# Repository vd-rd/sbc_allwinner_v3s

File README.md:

# Allwinner V3s SBC

This board embeds a SIP (single core 1GHz Cortex-A7 with 64MB DDR2) with AXP203 PMIC, IO headers and microSD/eMMC storage.

Board overview (draft):
[TBD]

## Board features
| Characteristic | Description |
| --- | --- |
| Dimensions | 60mm x 40mm |
| Processor | Allwinner V3s Cortex-A7 @1GHz |
| Oscillators | 32.768kHz slow click, 24MHz main clock |
| RAM | 512Mb embedded DDR2 memory |
| Storage | SPI Flash/microSD |
| USB | 1 microUSB OTG |
| Ethernet | 10/100M PHY with pins on header |
| Supply | Power path between USB/Vin/Battery, 5V max |

## Notes and observations

### Expansions
The board features a number of connectors. They expose various buses for expansions:
 * 1 SPI port
 * 2 UART ports
 * 1 I2C port
 * 2 ADC enabled pins
 * 18bit parallel LCD interface
 * Ethernet signals with status LEDs

The connectors are organized in consistent locations present on the other SBCs i have developed.
 * J100 connector - 2.54mm 2x18 header with standard Apollo IoT pinout
 * J200 connector - 1.27mm 2x04 header with ethernet signals
 * J300 connector - 1.27mm 2x05 header with analog audio I/O signals
 * J500 connector - 1.27mm 2x20 header with parallel LCD interface signals

Check expansions section for example daughter cards with added functionality

### Boot process
The board has two boot strategies depending on component configuration. If the SPI flash memory is not used, the BROM uses the MicroSD as boot source and loads UBoot from there.
If the SPI flash is populated, UBoot with a minimal Kernel and Busybox can be stored as recovery environment or main application.

### LCD connector
Most of port D signals are mapped to the LCD connector. if LCD is not used they can be muxed as GPIO or other functions upon editing the DT overlay.

### AXP203
AXP203 is pin to pin compatible with the more popular AXP209, so they can be easily swapped.

### 1.2V Rail
Two different 1.2V rails are provided to the CPU. This is a deliberate decision to allow fixed CPU internal rail at 1.2V and provide DVFS cappability to 1.2V rail for CPU core.

### Signals on headers
All the signals on the headers, with their initial functions are detailed on the silkscreen on the bottom layer

### Battery usage
The board schematic uses a Diodes AP9211 battery protection IC for safety protections when used toghether with a LiIon battery. If a battery pack with embedded protection and thermistor is used, TH1 and AP9211 can be left unpopulated.

### Expansions
 The board can be combined with several predefined capes that add functionality.
 * [LCD cape](https://github.com/vd-rd/hw_cape_lcd) can be used to add a 3inch LCD/Touch with 800x480px resolution.
 * [GPS cape](https://github.com/vd-rd/hw_cape_gps) adds GPS/GNSS/GLONAS capabilities
 * [GSM cape](https://github.com/vd-rd/hw_cape_gsm) adds GPRS connectivity. 

## Resources
You can find all necesary information to build or evaluate the module here:
   - [View 3D board render](https://a360.co/2GTPupk)
   - [Fabrication files](https://github.com/vd-rd/sbc_alw_v3s/releases)

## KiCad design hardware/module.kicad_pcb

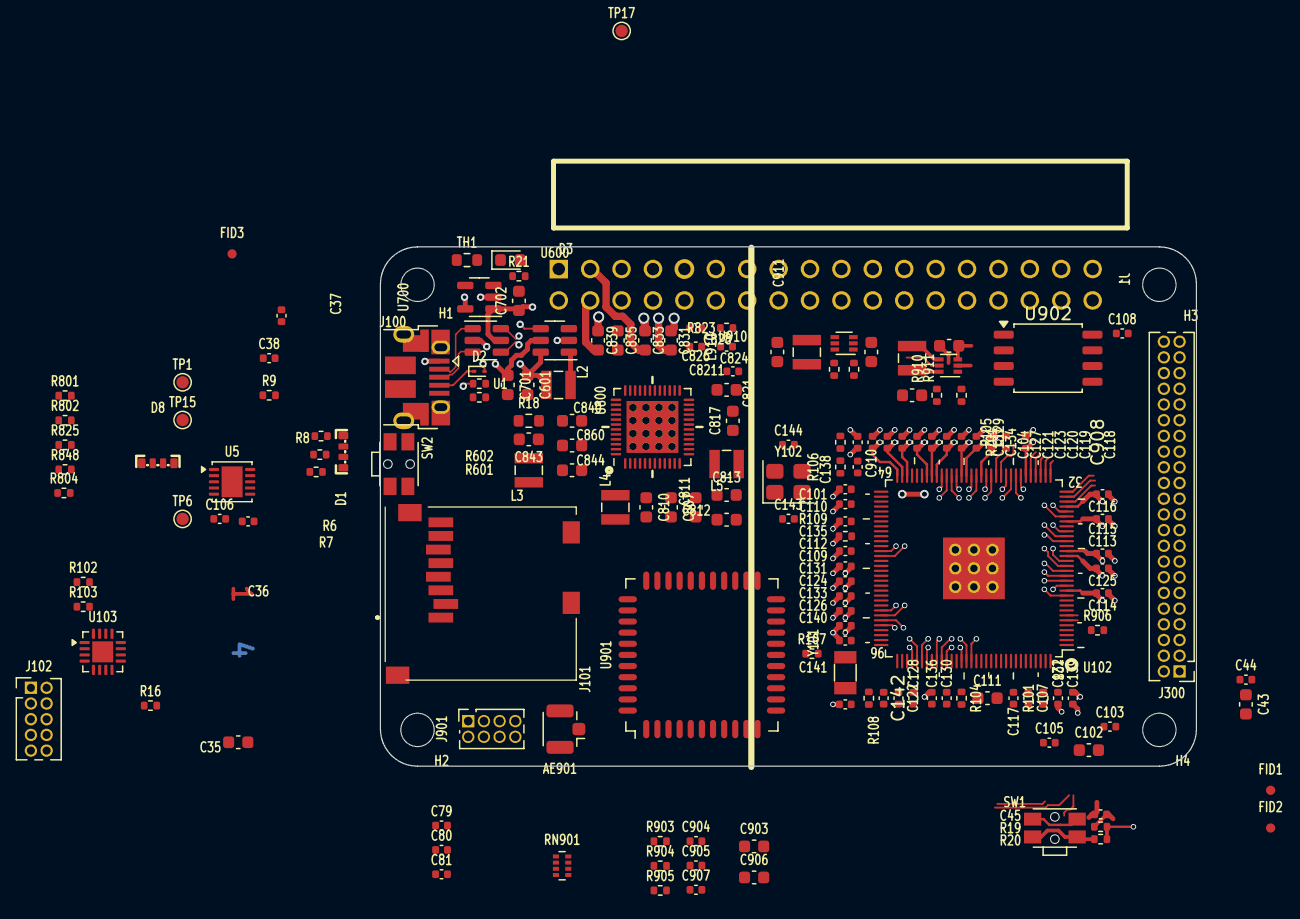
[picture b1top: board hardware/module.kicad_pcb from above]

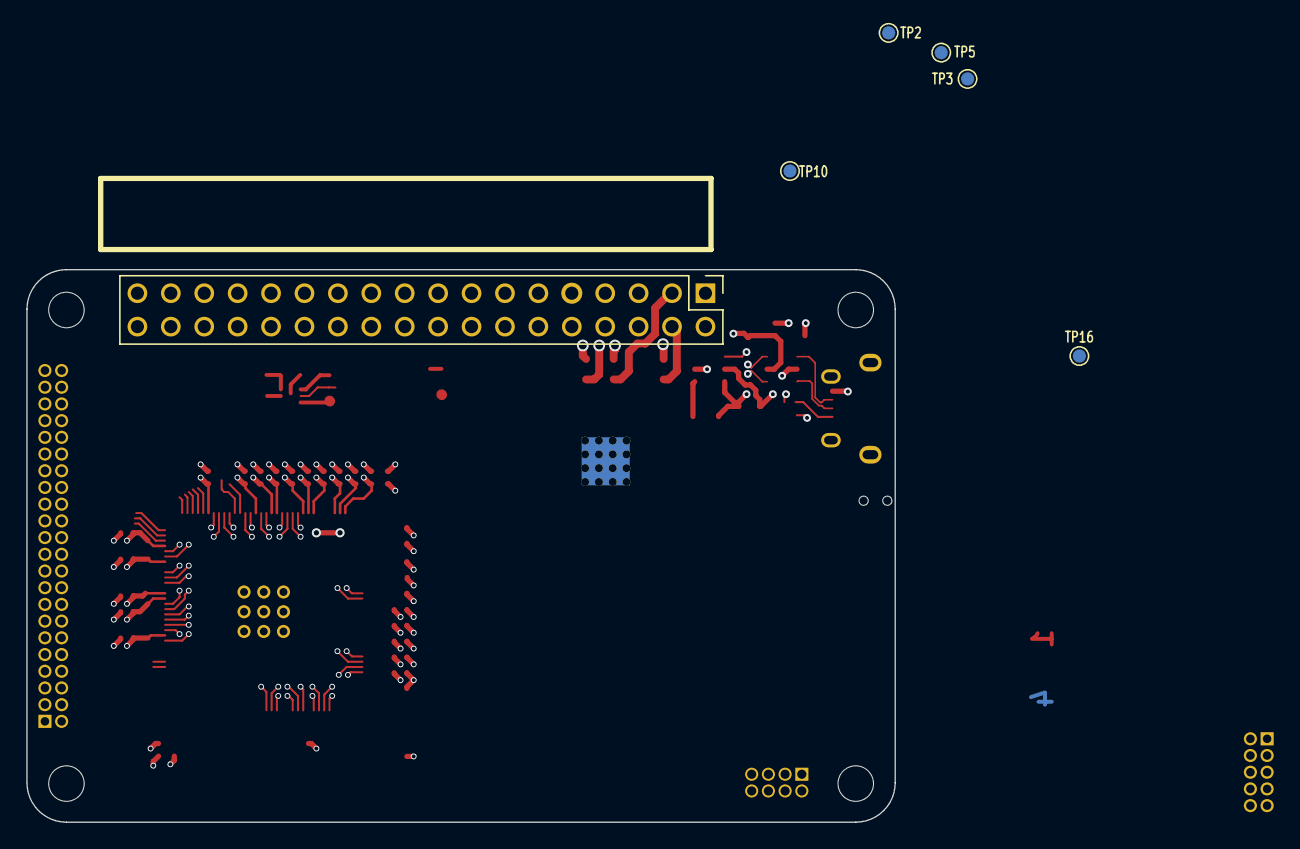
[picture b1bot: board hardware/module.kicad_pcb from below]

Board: 4 copper layers, 66.0 x 42.0 mm, 171 parts (6 on the bottom side), 137 nets.

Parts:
AE901: Antenna_Shield; U.FL_Hirose_U.FL-R-SMT-1_Vertical
C35: 100nF; C_0603_1608Metric
C36, C79, C81, C103, C104, C106, C107, C108, C113, C114, C115, C116, C117, C118, C119, C120, C121, C122, C123, C124, C125, C126, C127, C128, C129, C130, C131, C132, C133, C136, C824, C826, C828, C908: 1uF; C_0402_1005Metric
C37, C38, C44, C45, C80, C101, C105, C109, C112, C134, C135, C137, C138, C139, C904, C905, C907, C8211: 100nF; C_0402_1005Metric
C43, C102, C111, C601, C701, C702, C807, C810, C813, C817, C831, C833, C835, C839, C840, C843, C901, C902, C910, C911: 10uF; C_0603_1608Metric
C110: 1nF; C_0402_1005Metric
C140, C141, C143, C144: 22pF; C_0402_1005Metric
C142: 4.7uF; C_0402_1005Metric
C811, C812, C821, C844, C860, C903, C906: 4.7uF; C_0603_1608Metric
D1, D8: LED_RGBA; rgb-1204
D2: ESD9B5.0ST5G; D_SOD-923
D3: LED_Small; LED_0603_1608Metric
FID1, FID2, FID3: Fiducial; Fiducial_0.75mm_Mask1.5mm
H1, H2, H3, H4: MountingHole; MountingHole_2.7mm_M2.5_DIN965
J1: Conn_02x18_Odd_Even; PinHeader_2x18_P2.54mm_Vertical
J100: USB_B_Micro; USB_Micro-B_Amphenol_10103594-0001LF_Horizontal
J101: Micro_SD_Card_Det; MEM20610118800A
J102: Conn_02x05_Odd_Even; PinHeader_2x05_P1.27mm_Vertical
J300: Conn_02x22_Odd_Even; PinHeader_2x22_P1.27mm_Vertical
J901: Conn_01x08; PinSocket_2x04_P1.27mm_Vertical
L1, L910: 1uH; L_Wuerth_MAPI-2510
L2: 4.7uH; L_Wuerth_MAPI-2510
L3, L4, L5: 4.7uH; L_Wuerth_MAPI-2512
R6, R7, R8: 180; R_0402_1005Metric
R9: 1k; R_0402_1005Metric
R16, R825, R848: 47k; R_0402_1005Metric
R18: 30m; R_0603_1608Metric
R19: 100k; R_0402_1005Metric
R20: 6.8k; R_0402_1005Metric
R21, R102, R105, R106, R804: 2.2k; R_0402_1005Metric
R101, R901, R911: 200k; R_0402_1005Metric
R103, R104: 0; R_0402_1005Metric
R107: 6.04k; R_0402_1005Metric
R108: 10M; R_0402_1005Metric
R109: 240; R_0402_1005Metric
R601: 976k; R_0402_1005Metric
R602: 562k; R_0402_1005Metric
R701: 100K; R_0402_1005Metric
R801, R802: 1.8k; R_0402_1005Metric
R823: 200K; R_0402_1005Metric
R902: 133k; R_0402_1005Metric
R903, R904, R905: 33k; R_0402_1005Metric
R906: 22; R_0402_1005Metric
R910: R_0402_1005Metric
RN901: 33k; R_Array_Concave_4x0402
SW1, SW2: SW_Push; SW_SPST_EVQP7C
TH1: Thermistor_NTC; R_0603_1608Metric
TP1, TP2, TP3, TP5, TP6, TP10, TP15, TP16, TP17: TestPoint; TestPoint_Pad_D1.0mm
U1: USBLC6-2P6; SOT-23-6
U5: IS31FL3193; DFN-10-1EP_3x3mm_P0.5mm_EP1.7x2.5mm
U102: V3s; QFP-128_14x14_Pitch0.4mm
U103: PCA6408A; QFN-16-1EP_3x3mm_P0.5mm_EP1.7x1.7mm
U600: MCP1640CH; SOT-23-6
U700: AP22811; SOT-23-5
U800: AXP209; QFN-48-1EP_6x6mm_P0.4mm_EP4.2x4.2mm_ThermalVias
U900, U910: AP61100; SOT-563
U901: RTL8723BS; lga44_12x12mm_P0.9
U902: W25Q128JVS; SOIC-8_5.3x5.3mm_P1.27mm
Y101: Crystal_Small; Crystal_SMD_3215-2Pin_3.2x1.5mm
Y102: 24MHz; Crystal_SMD_3225-4Pin_3.2x2.5mm

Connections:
+1V2_CPU: C810.1, L4.2, TP15.1, U800.10 (DCDC2)
+1V2_INT: C817.1, L5.2, TP2.1, U800.17 (DCDC3)
+1V5: C902.1, L1.2, R901.1, TP17.1, U900.6 (OUT)
+1V8: C101.1, C104.1, C109.1, C110.1, C137.1, R105.2, U102.59 (VCC-DRAM), U102.60 (VCC-DRAM), U102.61 (VCC-DRAM), U102.62 (VCC-DRAM), U102.65 (VCC-DRAM), U102.66 (VCC-DRAM), U102.67 (VCC-DRAM), U102.68 (VCC-DRAM), U102.69 (VCC-DRAM), U102.70 (VCC-DRAM), U102.72 (VCC-DRAM), U102.79 (VCC-DRAM)
+3V0: C45.1, C111.1, C112.1, C812.1, R19.1, TP3.1, U102.76 (VCC-PLL), U102.115 (AVCC), U800.12 (LDO2), U900.5 (EN)
+3V3: C35.1, C36.1, C79.1, C80.1, C81.1, C106.1, C108.1, C114.1, C116.1, C119.1, C121.1, C124.1, C126.1, C128.1, C130.1, C132.1, C903.1, C904.1, C905.1, C906.1, C907.1, C911.1, D1.4 (A), D8.4 (A), J1.2, J101.P4 (VDD), J300.43, L910.2, R16.1, R102.2, R801.1, R802.1, R825.1, R848.1, R903.2, R904.2, R905.2, R910.1, RN901.1 (R1.1), RN901.2 (R2.1), RN901.3 (R3.1), RN901.4 (R4.1), TP5.1, U5.2 (VCC), U102.12 (VCC-PE), U102.29 (VCC-PE), U102.50 (VCC-IO), U102.57 (VCC-IO), U102.85 (VCC-MCSI), U102.93 (EPHY-VCC), U102.104 (VCC-IO), U102.109 (VCC-USB), U102.122 (HPVCCIN), U102.127 (VCC-IO), U103.14 (VDD-P), U103.15 (VDD-BUS), U901.9 (VBAT), U901.22 (VDDIO), U902.8 (VCC), U910.6 (OUT)
+3V3_LDO: C43.1, C44.1, J300.8, TP6.1
+3V3_RTC: C122.1, C828.1, U102.98 (VCC-RTC), U800.28 (LDO1)
+3V3_periph: C811.1, U800.11 (LDO4)
+5V_USB: C37.1, C702.1, C831.1, J100.1 (VBUS), U1.5 (VBUS), U700.1 (OUT), U800.31 (VBUS)
/CPU Signals/Vhp_bp: C102.1, C105.1, U102.123 (HPVCCBP)
/CPU Signals/hpcom: J102.2, U102.125 (HPCOM)
/CPU Signals/hpcomfb: C103.1, R103.1, U102.124 (HPCOMFB)
/CPU Signals/hpoutl: J102.4, U102.121 (HPOUTL)
/CPU Signals/hpoutr: J102.3, U102.120 (HPOUTR)
/CPU Signals/hse-in: C144.1, U102.75 (X24MIN), Y102.3
/CPU Signals/hse-out: C143.1, U102.74 (X24MOUT), Y102.1
/CPU Signals/lse-in: C141.1, R108.1, U102.96 (X32KIN), Y101.2
/CPU Signals/lse-out: C140.1, R108.2, U102.95 (X32KOUT), Y101.1
/CPU Signals/mic_bias: J102.9, U102.119 (HBIAS)
/CPU Signals/micin+: J102.8, U102.113 (MICIN1P)
/CPU Signals/micin-: R104.1, U102.114 (MICIN1N)
/CPU Signals/svref: C134.1, C135.1, C137.2, C138.1, R105.1, R106.2, U102.63 (SVREF), U102.71 (SVREF)
/CPU Signals/vra1: C117.1, U102.117 (VRA1)
/CPU Signals/vra2: C107.1, R101.2, U102.118 (VRA2)
/IO Connectors/usb-d+: J100.3 (D+), U1.3 (I/O2)
/IO Connectors/usb-d-: J100.2 (D-), U1.1 (I/O1)
/PMIC & power rails/lx1: C843.1, L3.2, R18.1, U800.43 (CHSENSE)
/PMIC & power rails/pmu_en: R804.2, TP1.1, U800.4 (~OE)
/PMIC & power rails/vint: C826.1, U800.26 (VINT), U800.27 (LDO1SET)
ACIN: C833.1, J1.3, U800.32 (ACIN), U800.33 (ACIN)
AP_WAKE_BT: U103.4 (IO2), U901.6 (BT_WAKE)
BAT_NTC: J1.6, TH1.1, U800.37 (TS)
BT_DISABLE: R905.1, U103.3 (IO1), U901.34 (BT_REG_ON)
BT_WAKE_AP: U103.8 (IO5), U901.7 (BT_HOST_WAKE)
BUTTON: R19.2, R20.1
EPHY-LINK: J901.2, U102.77 (EPHY-LINK-LED)
EPHY-RX+: J901.3, U102.90 (EPHY-RXP)
EPHY-RX-: J901.4, U102.89 (EPHY-RXN)
EPHY-SPD: J901.6, U102.78 (EPHY-SPD-LED)
EPHY-TX+: J901.7, U102.92 (EPHY-TXP)
EPHY-TX-: J901.8, U102.91 (EPHY-TXN)
EXTEN: TP10.1, U800.20 (EXTEN), U910.5 (EN)
GND: AE901.2 (Shield), C35.2, C36.2, C37.2, C38.2, C43.2, C44.2, C45.2, C79.2, C80.2, C81.2, C101.2, C102.2, C103.2, C104.2, C105.2, C106.2, C107.2, C108.2, C109.2, C110.2, C111.2, C112.2, C113.2, C114.2, C115.2, C116.2, C117.2, C118.2, C119.2, C120.2, C121.2, C122.2, C123.2, C124.2, C125.2, C126.2, C127.2, C128.2, C129.2, C130.2, C131.2, C132.2, C133.2, C134.2, C135.2, C136.2, C138.2, C139.2, C140.2, C141.2, C142.2, C143.2, C144.2, C601.2, C701.2, C702.2, C807.2, C810.2, C811.2, C812.2, C813.2, C817.2, C821.2, C824.2, C826.2, C828.2, C831.2, C833.2, C835.2, C839.2, C840.2, C843.2, C844.2, C860.2, C901.2, C902.2, C903.2, C904.2, C905.2, C906.2, C907.2, C908.2, C910.2, C911.2, C8211.2, D2.2 (A2), J1.1, J1.5, J1.14, J1.23, J1.36, J100.5 (GND), J100.6 (Shield), J101.G1 (SHIELD), J101.G2 (SHIELD), J101.P6 (VSS), J102.1, J102.10, J300.1, J300.10, J300.11, J300.18, J300.19, J300.26, J300.27, J300.34, J300.35, J300.36, J300.37, J300.44, J901.1, J901.5, R101.1, R103.2, R104.2, R106.1, R107.2, R109.2, R602.2, R701.2, R804.1, R823.2, R902.2, R911.2, SW1.1, SW2.1, TH1.2, U1.2 (GND), U5.6 (GND), U5.7 (AD), U5.11 (GND), U102.116 (AGND), U102.129 (GND), U103.6 (VSS), U103.16 (ADDR), U600.2 (GND), U700.2 (GND), U800.9 (PGND2), U800.16 (PGND3), U800.22 (AGND), U800.46 (PGND1), U800.49 (EP), U900.2 (GND), U901.1 (GND), U901.3 (GND), U901.20 (GND), U901.31 (GND), U901.33 (GND), U901.36 (GND), U901.41 (GND), U902.4 (GND), U910.2 (GND)
GPIO1: J1.13, U103.9 (IO6)
GPIO2: J1.20, U103.10 (IO7)
GPIO3: J1.19, U103.2 (IO0)
GPIOA1: J1.31, U800.19 (GPIO0)
GPIOA2: J1.32, U800.18 (GPIO1)
GPIO_INT: R102.1, U102.42 (PB3), U103.11 (~INT)
I2C-SCL: J1.17, U5.8 (SCL), U102.45 (PB6), U103.12 (SCL)
I2C-SDA: J1.18, U5.9 (SDA), U102.46 (PB7), U103.13 (SDA)
IPS: C601.1, C807.1, C813.1, C821.1, C835.1, C840.1, C844.1, C901.1, C910.1, C8211.1, D3.2 (A), L2.2, TP16.1, U600.6 (VIN), U800.7 (VIN2), U800.13 (LDO24IN), U800.14 (VIN3), U800.21 (APS), U800.34 (IPSOUT), U800.35 (IPSOUT), U800.40 (LDO3IN), U800.44 (VIN1), U900.3 (VIN), U910.3 (VIN)
LCD-CLK: J300.39, U102.37 (PE0)
LCD-D2: J300.33, U102.33 (PE4)
LCD-D3: J300.32, U102.32 (PE5)
LCD-D4: J300.31, U102.31 (PE6)
LCD-D5: J300.30, U102.30 (PE7)
LCD-D6: J300.29, U102.28 (PE8)
LCD-D7: J300.28, U102.27 (PE9)
LCD-D10: J300.25, U102.24 (PE10)
LCD-D11: J300.24, U102.23 (PE11)
LCD-D12: J300.23, U102.22 (PE12)
LCD-D13: J300.22, U102.18 (PE13)
LCD-D14: J300.21, U102.17 (PE14)
LCD-D15: J300.20, U102.16 (PE15)
LCD-D18: J300.17, U102.15 (PE16)
LCD-D19: J300.16, U102.14 (PE17)
LCD-D20: J300.15, U102.13 (PE18)
LCD-D21: J300.14, U102.11 (PE19)
LCD-D22: J300.13, U102.7 (PE23)
LCD-D23: J300.12, U102.6 (PE24)
LCD-DE: J300.38, U102.36 (PE1)
LCD-HSYNC: J300.40, U102.35 (PE2)
LCD-VSYNC: J300.41, U102.34 (PE3)
LCD_BL: J300.42, U102.43 (PB4)
NMI: R848.2, U102.41 (PB2), U800.48 (IRQ)
unnamed: AE901.1 (A), U901.2 (WL_BT_ANT)
unnamed: D1.3 (BK), R8.2
unnamed: D1.1 (GK), R7.2
unnamed: D1.2 (RK), R6.2
unnamed: D3.1 (K), R21.1
unnamed: D8.3 (BK), U5.5 (OUT3)
unnamed: D8.2 (GK), U5.4 (OUT2)
unnamed: D8.1 (RK), U5.3 (OUT1)
unnamed: R9.2, SW2.2
unnamed: R20.2, SW1.2
unnamed: C142.1, U102.97 (RTC-VIO)
unnamed: R109.1, U102.73 (SZQ)
unnamed: R107.1, U102.94 (EPHY-RTX)
unnamed: L2.1, U600.1 (SW)
unnamed: R601.2, R602.1, U600.4 (VFB)
unnamed: C701.1, R601.1, U600.5 (VOUT), U700.5 (IN)
unnamed: R823.1, U800.23 (BIAS)
unnamed: R21.2, U800.36 (CHGLED)
unnamed: C860.1, U800.41 (LDO3)
unnamed: L3.1, U800.45 (LX1)
unnamed: L4.1, U800.8 (LX2)
unnamed: L5.1, U800.15 (LX3)
unnamed: C824.1, U800.24 (VREF)
unnamed: R901.2, R902.1, U900.1 (FB)
unnamed: L1.1, U900.4 (SW)
unnamed: R906.2, U901.17 (SDIO_CLK)
unnamed: R910.2, R911.1, U910.1 (FB)
unnamed: L910.1, U910.4 (SW)
PMU-VBUSEN: R701.1, U102.44 (PB5), U600.3 (EN), U700.4 (EN), U800.6 (~VBUSEN)
PWRON: C38.1, R9.1, U800.47 (PWRON)
RSB-SCK: J300.6, R802.2, U800.2 (SCK)
RSB-SDA: J300.7, R801.2, U800.1 (SDA)
SDC0-CLK: J101.P5 (CLK), U102.105 (PF2)
SDC0-CMD: J101.P3 (CMD), U102.103 (PF3)
SDC0-D0: J101.P7 (DAT0), U102.106 (PF1)
SDC0-D1: J101.P8 (DAT1), U102.107 (PF0)
SDC0-D2: J101.P1 (DAT2), U102.101 (PF5)
SDC0-D3: J101.P2 (DAT3/CD), U102.102 (PF4)
SDC0-DET: J101.CD1 (DET_A), J101.CD2 (DET_B), U102.100 (PF6)
SDC1-CLK: R906.1, U102.5 (PG0)
SDC1-CMD: RN901.6 (R3.2), U102.4 (PG1), U901.16 (SDIO_CMD)
SDC1-D0: RN901.7 (R2.2), U102.3 (PG2), U901.18 (SDIO_DATA0)
SDC1-D1: RN901.8 (R1.2), U102.2 (PG3), U901.19 (SDIO_DATA1)
SDC1-D2: R903.1, U102.1 (PG4), U901.14 (SDIO_DATA2)
SDC1-D3: RN901.5 (R4.2), U102.128 (PG5), U901.15 (SDIO_DATA3)
SPI-CLK: J1.25, U102.53 (PC1), U902.6 (CLK)
SPI-CS: U102.54 (PC2), U902.1 (~CS)
SPI-MISO: J1.28, U102.52 (PC0), U902.2 (DO/IO_{1})
SPI-MOSI: J1.27, U102.55 (PC3), U902.5 (DI/IO_{0})
UART1-RX: U102.8 (PE22), U901.42 (UART_TXD)
UART1-TX: U102.9 (PE21), U901.43 (UART_RXD)
UART2-RX: J1.22, U102.40 (PB1)
UART2-TX: J1.21, U102.39 (PB0)
USB0_ID: D2.1 (A1), J100.4 (ID), R16.2
VBAT: C839.1, J1.4, R18.2, U800.38 (BAT), U800.39 (BAT), U800.42 (BATSENSE)
VDD_CPU: C113.1, C115.1, C118.1, C120.1, C123.1, C908.1, U102.20 (VDD-CPU), U102.21 (VDD-CPU), U102.25 (VDD-CPU), U102.26 (VDD-CPU), U102.38 (VDD-CPU), U102.47 (VDD-CPU), U102.51 (VDD-CPU), U102.56 (VDD-CPU)
VDD_SYS: C125.1, C127.1, C129.1, C131.1, C133.1, C136.1, C139.1, U102.19 (VDD-SYS), U102.58 (VDD-SYS), U102.64 (VDD-SYS), U102.80 (VDD-SYS), U102.88 (EPHY-VDD), U102.108 (VDD-SYS), U102.126 (VDD-SYS)
WL_HOST_WAKE: U103.5 (IO3), U901.13 (WL_HOST_WAKE)
WL_REG_ON: R904.1, U103.7 (IO4), U901.12 (WL_REG_ON)
~RST: J1.7, R825.2, U102.99 (RESET), U103.1 (~RESET), U800.25 (POWOK)

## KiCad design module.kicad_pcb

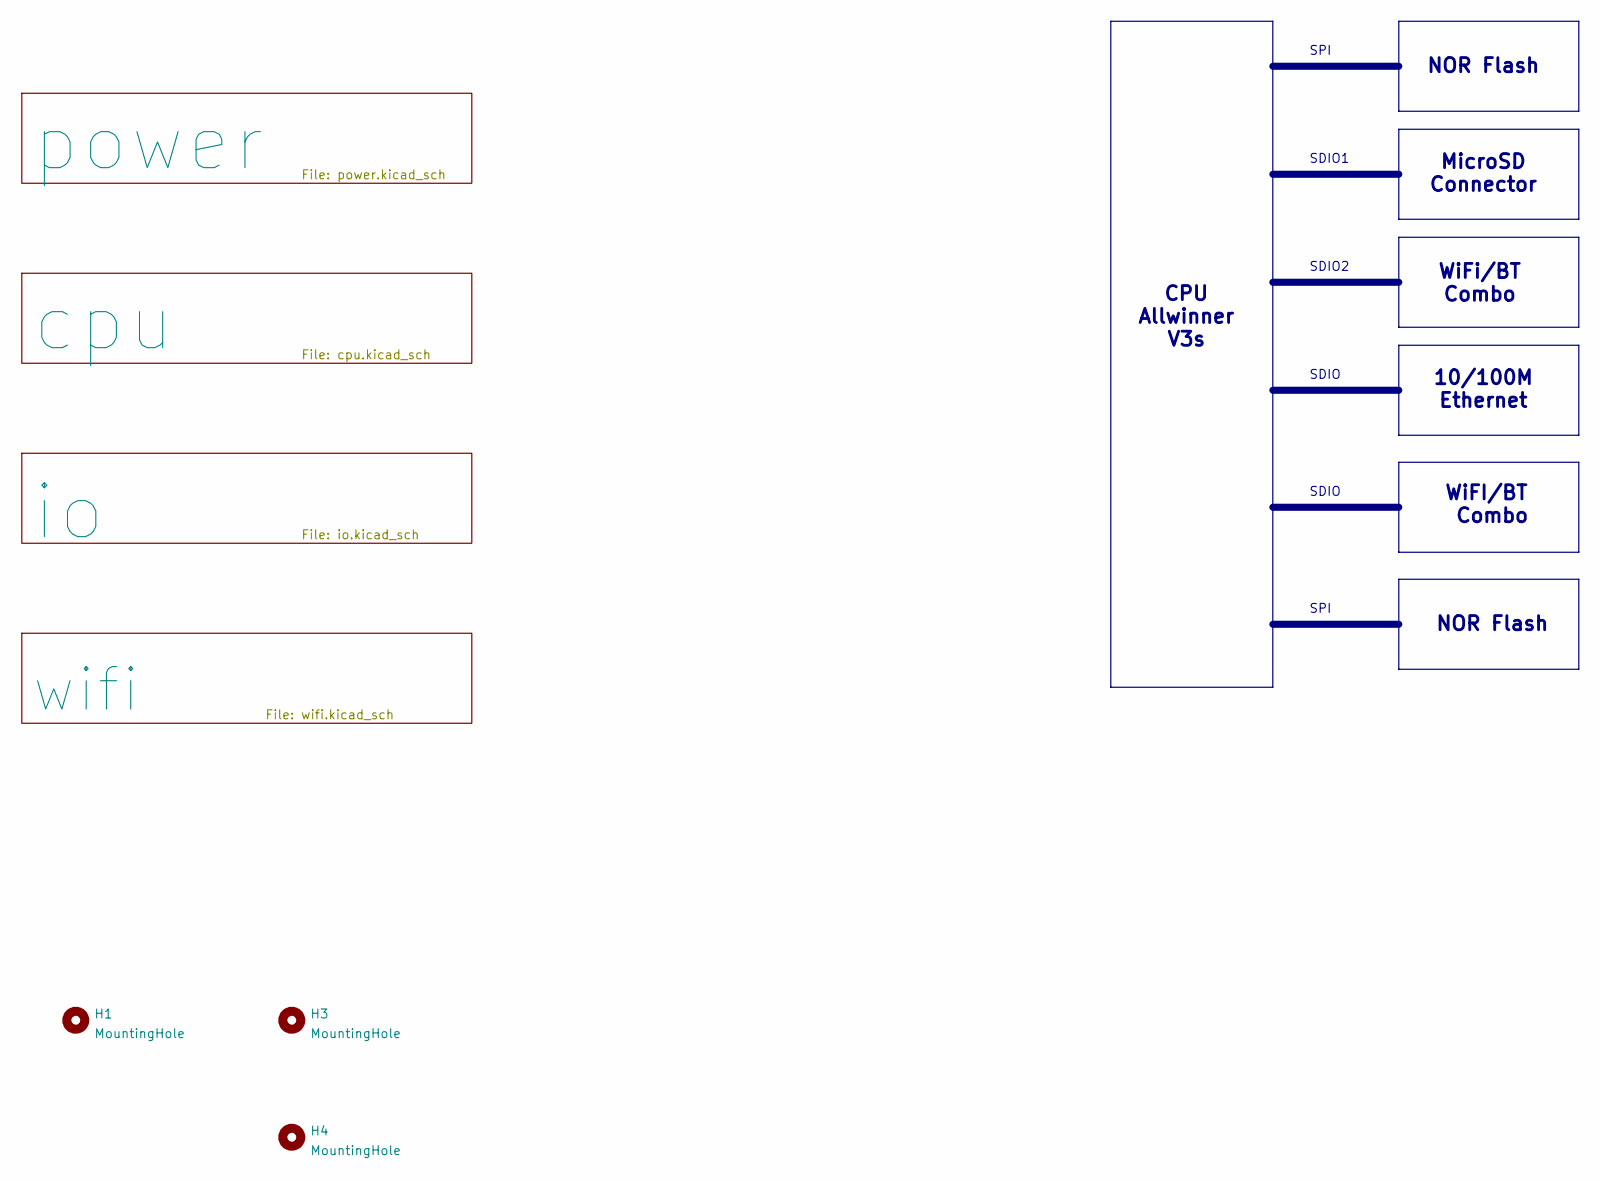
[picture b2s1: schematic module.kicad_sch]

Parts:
H1, H3, H4: MountingHole; MountingHole_2.7mm_M2.5

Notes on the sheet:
NOR Flash
10/100M Ethernet
WiFi/BT Combo
SPI
WiFI/BT Combo
SDIO
MicroSD Connector
SDIO1
CPU Allwinner V3s
SDIO2

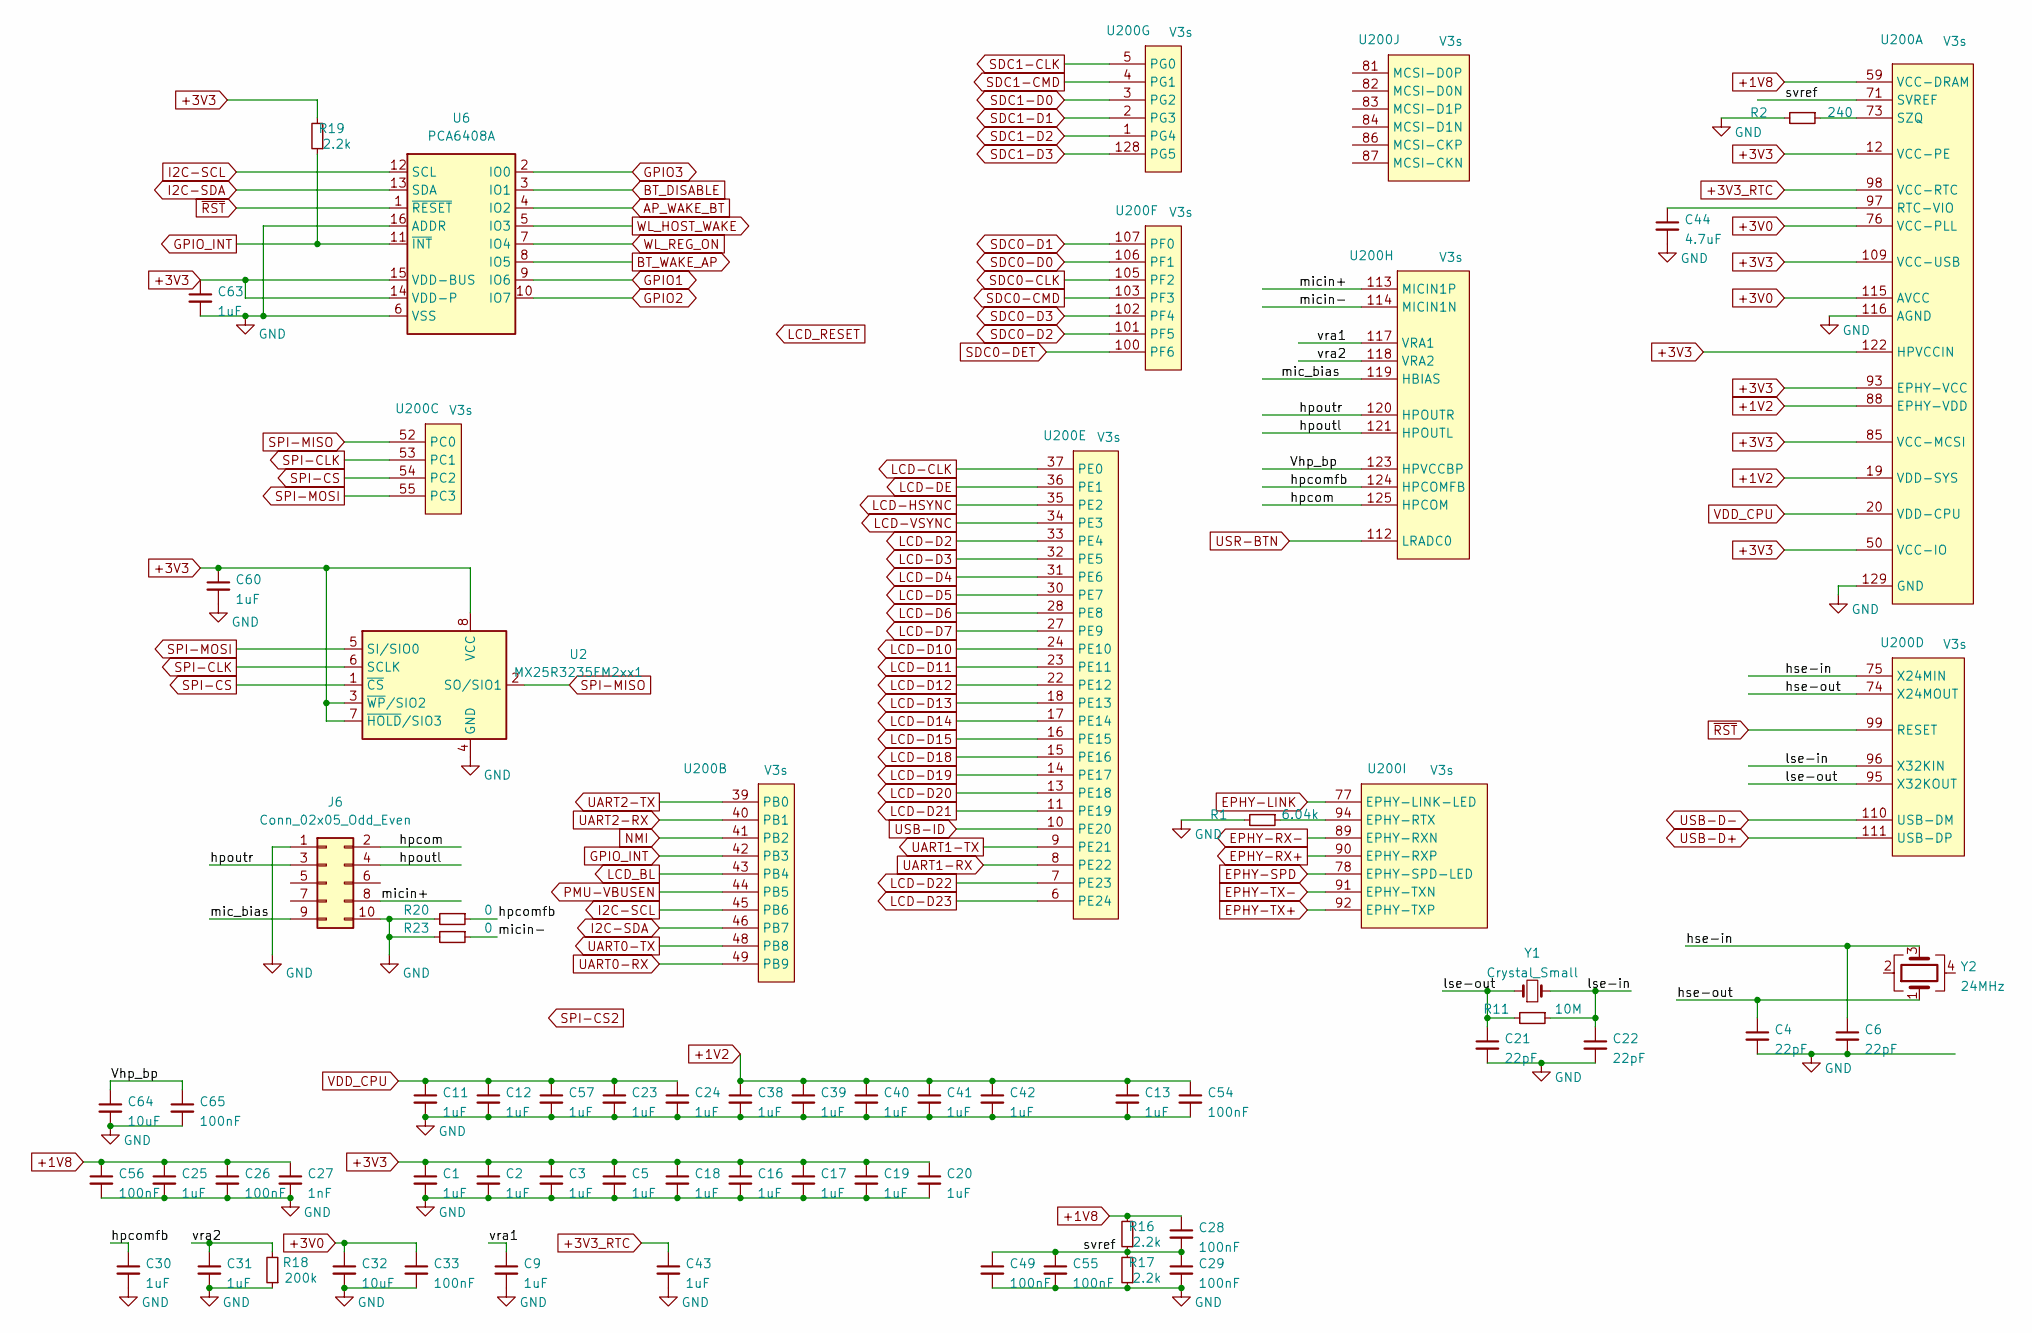
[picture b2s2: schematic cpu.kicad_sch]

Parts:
C1, C2, C3, C5, C9, C11, C12, C13, C16, C17, C18, C19, C20, C23, C24, C25, C30, C31, C38, C39, C40, C41, C42, C43, C57, C60, C63: 1uF; C_0402_1005Metric
C4, C6, C21, C22: 22pF; C_0402_1005Metric
C26, C28, C29, C33, C49, C54, C55, C56, C65: 100nF; C_0402_1005Metric
C27: 1nF; C_0402_1005Metric
C32, C64: 10uF; C_0603_1608Metric
C44: 4.7uF; C_0603_1608Metric
J6: Conn_02x05_Odd_Even; PinHeader_2x05_P1.27mm_Vertical
R1: 6.04k; R_0402_1005Metric
R2: 240; R_0402_1005Metric
R11: 10M; R_0402_1005Metric
R16, R17, R19: 2.2k; R_0402_1005Metric
R18: 200k; R_0402_1005Metric
R20, R23: 0; R_0402_1005Metric
U2: MX25R3235FM2xx1; SOP-8_5.28x5.23mm_P1.27mm
U6: PCA6408A; QFN-16-1EP_3x3mm_P0.5mm_EP1.7x1.7mm
U200: V3s; QFP-128_14x14_Pitch0.4mm
Y1: Crystal_Small; Crystal_SMD_3215-2Pin_3.2x1.5mm
Y2: 24MHz; Crystal_SMD_3225-4Pin_3.2x2.5mm

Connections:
+1V2: C13.1, C38.1, C39.1, C40.1, C41.1, C42.1, C54.1, U200.19 (VDD-SYS), U200.58 (VDD-SYS), U200.64 (VDD-SYS), U200.80 (VDD-SYS), U200.88 (EPHY-VDD), U200.108 (VDD-SYS), U200.126 (VDD-SYS); also elsewhere on the board
+1V8: C25.1, C26.1, C27.1, C28.1, C56.1, R16.2, U200.59 (VCC-DRAM), U200.60 (VCC-DRAM), U200.61 (VCC-DRAM), U200.62 (VCC-DRAM), U200.65 (VCC-DRAM), U200.66 (VCC-DRAM), U200.67 (VCC-DRAM), U200.68 (VCC-DRAM), U200.69 (VCC-DRAM), U200.70 (VCC-DRAM), U200.72 (VCC-DRAM), U200.79 (VCC-DRAM)
+3V0: C32.1, C33.1, U200.76 (VCC-PLL), U200.115 (AVCC); also elsewhere on the board
+3V3: C1.1, C2.1, C3.1, C5.1, C16.1, C17.1, C18.1, C19.1, C20.1, C60.1, C63.1, R19.2, U2.3 (~WP/SIO2), U2.7 (~HOLD/SIO3), U2.8 (VCC), U6.14 (VDD-P), U6.15 (VDD-BUS), U200.12 (VCC-PE), U200.29 (VCC-PE), U200.50 (VCC-IO), U200.57 (VCC-IO), U200.85 (VCC-MCSI), U200.93 (EPHY-VCC), U200.104 (VCC-IO), U200.109 (VCC-USB), U200.122 (HPVCCIN), U200.127 (VCC-IO); also elsewhere on the board
+3V3_RTC: C43.1, U200.98 (VCC-RTC); also elsewhere on the board
/cpu/Vhp_bp: C64.1, C65.1, U200.123 (HPVCCBP)
/cpu/hpcom: J6.2, U200.125 (HPCOM)
/cpu/hpcomfb: C30.1, R20.1, U200.124 (HPCOMFB)
/cpu/hpoutl: J6.4, U200.121 (HPOUTL)
/cpu/hpoutr: J6.3, U200.120 (HPOUTR)
/cpu/hse-in: C6.1, U200.75 (X24MIN), Y2.3
/cpu/hse-out: C4.1, U200.74 (X24MOUT), Y2.1
/cpu/lse-in: C22.1, R11.1, U200.96 (X32KIN), Y1.2
/cpu/lse-out: C21.1, R11.2, U200.95 (X32KOUT), Y1.1
/cpu/mic_bias: J6.9, U200.119 (HBIAS)
/cpu/micin+: J6.8, U200.113 (MICIN1P)
/cpu/micin-: R23.1, U200.114 (MICIN1N)
/cpu/svref: C28.2, C29.1, C49.1, C55.1, R16.1, R17.2, U200.63 (SVREF), U200.71 (SVREF)
/cpu/vra1: C9.1, U200.117 (VRA1)
/cpu/vra2: C31.1, R18.2, U200.118 (VRA2)
AP_WAKE_BT: U6.4 (IO2); also elsewhere on the board
BT_DISABLE: U6.3 (IO1); also elsewhere on the board
BT_WAKE_AP: U6.8 (IO5); also elsewhere on the board
EPHY-LINK: U200.77 (EPHY-LINK-LED); also elsewhere on the board
EPHY-RX+: U200.90 (EPHY-RXP); also elsewhere on the board
EPHY-RX-: U200.89 (EPHY-RXN); also elsewhere on the board
EPHY-SPD: U200.78 (EPHY-SPD-LED); also elsewhere on the board
EPHY-TX+: U200.92 (EPHY-TXP); also elsewhere on the board
EPHY-TX-: U200.91 (EPHY-TXN); also elsewhere on the board
GND: C1.2, C2.2, C3.2, C4.2, C5.2, C6.2, C9.2, C11.2, C12.2, C13.2, C16.2, C17.2, C18.2, C19.2, C20.2, C21.2, C22.2, C23.2, C24.2, C25.2, C26.2, C27.2, C29.2, C30.2, C31.2, C32.2, C33.2, C38.2, C39.2, C40.2, C41.2, C42.2, C43.2, C44.2, C49.2, C54.2, C55.2, C56.2, C57.2, C60.2, C63.2, C64.2, C65.2, J6.1, J6.10, R1.2, R2.2, R17.1, R18.1, R20.2, R23.2, U2.4 (GND), U6.6 (VSS), U6.16 (ADDR), U200.116 (AGND), U200.129 (GND); also elsewhere on the board
GPIO1: U6.9 (IO6)
GPIO2: U6.10 (IO7)
GPIO3: U6.2 (IO0)
GPIO_INT: R19.1, U6.11 (~INT), U200.42 (PB3)
I2C-SCL: U6.12 (SCL), U200.45 (PB6); also elsewhere on the board
I2C-SDA: U6.13 (SDA), U200.46 (PB7); also elsewhere on the board
LCD-CLK: U200.37 (PE0); also elsewhere on the board
LCD-D2: U200.33 (PE4); also elsewhere on the board
LCD-D3: U200.32 (PE5); also elsewhere on the board
LCD-D4: U200.31 (PE6); also elsewhere on the board
LCD-D5: U200.30 (PE7); also elsewhere on the board
LCD-D6: U200.28 (PE8); also elsewhere on the board
LCD-D7: U200.27 (PE9); also elsewhere on the board
LCD-D10: U200.24 (PE10); also elsewhere on the board
LCD-D11: U200.23 (PE11); also elsewhere on the board
LCD-D12: U200.22 (PE12); also elsewhere on the board
LCD-D13: U200.18 (PE13); also elsewhere on the board
LCD-D14: U200.17 (PE14); also elsewhere on the board
LCD-D15: U200.16 (PE15); also elsewhere on the board
LCD-D18: U200.15 (PE16); also elsewhere on the board
LCD-D19: U200.14 (PE17); also elsewhere on the board
LCD-D20: U200.13 (PE18); also elsewhere on the board
LCD-D21: U200.11 (PE19); also elsewhere on the board
LCD-D22: U200.7 (PE23); also elsewhere on the board
LCD-D23: U200.6 (PE24); also elsewhere on the board
LCD-DE: U200.36 (PE1); also elsewhere on the board
LCD-HSYNC: U200.35 (PE2); also elsewhere on the board
LCD-VSYNC: U200.34 (PE3); also elsewhere on the board
LCD_BL: U200.43 (PB4); also elsewhere on the board
NMI: U200.41 (PB2)
unnamed: C44.1, U200.97 (RTC-VIO)
unnamed: R2.1, U200.73 (SZQ)
unnamed: R1.1, U200.94 (EPHY-RTX)
PMU-VBUSEN: U200.44 (PB5); also elsewhere on the board
SDC0-CLK: U200.105 (PF2); also elsewhere on the board
SDC0-CMD: U200.103 (PF3); also elsewhere on the board
SDC0-D0: U200.106 (PF1); also elsewhere on the board
SDC0-D1: U200.107 (PF0); also elsewhere on the board
SDC0-D2: U200.101 (PF5); also elsewhere on the board
SDC0-D3: U200.102 (PF4); also elsewhere on the board
SDC0-DET: U200.100 (PF6); also elsewhere on the board
SDC1-CLK: U200.5 (PG0); also elsewhere on the board
SDC1-CMD: U200.4 (PG1); also elsewhere on the board
SDC1-D0: U200.3 (PG2); also elsewhere on the board
SDC1-D1: U200.2 (PG3); also elsewhere on the board
SDC1-D2: U200.1 (PG4); also elsewhere on the board
SDC1-D3: U200.128 (PG5); also elsewhere on the board
SPI-CLK: U2.6 (SCLK), U200.53 (PC1)
SPI-CS: U2.1 (~CS), U200.54 (PC2)
SPI-MISO: U2.2 (SO/SIO1), U200.52 (PC0)
SPI-MOSI: U2.5 (SI/SIO0), U200.55 (PC3)
UART0-RX: U200.49 (PB9)
UART0-TX: U200.48 (PB8)
UART1-RX: U200.8 (PE22); also elsewhere on the board
UART1-TX: U200.9 (PE21); also elsewhere on the board
UART2-RX: U200.40 (PB1)
UART2-TX: U200.39 (PB0)
USB-D+: U200.111 (USB-DP); also elsewhere on the board
USB-D-: U200.110 (USB-DM); also elsewhere on the board
USB-ID: U200.10 (PE20); also elsewhere on the board
USR-BTN: U200.112 (LRADC0); also elsewhere on the board
VDD_CPU: C11.1, C12.1, C23.1, C24.1, C57.1, U200.20 (VDD-CPU), U200.21 (VDD-CPU), U200.25 (VDD-CPU), U200.26 (VDD-CPU), U200.38 (VDD-CPU), U200.47 (VDD-CPU), U200.51 (VDD-CPU), U200.56 (VDD-CPU); also elsewhere on the board
WL_HOST_WAKE: U6.5 (IO3); also elsewhere on the board
WL_REG_ON: U6.7 (IO4); also elsewhere on the board
~RST: U6.1 (~RESET), U200.99 (RESET); also elsewhere on the board

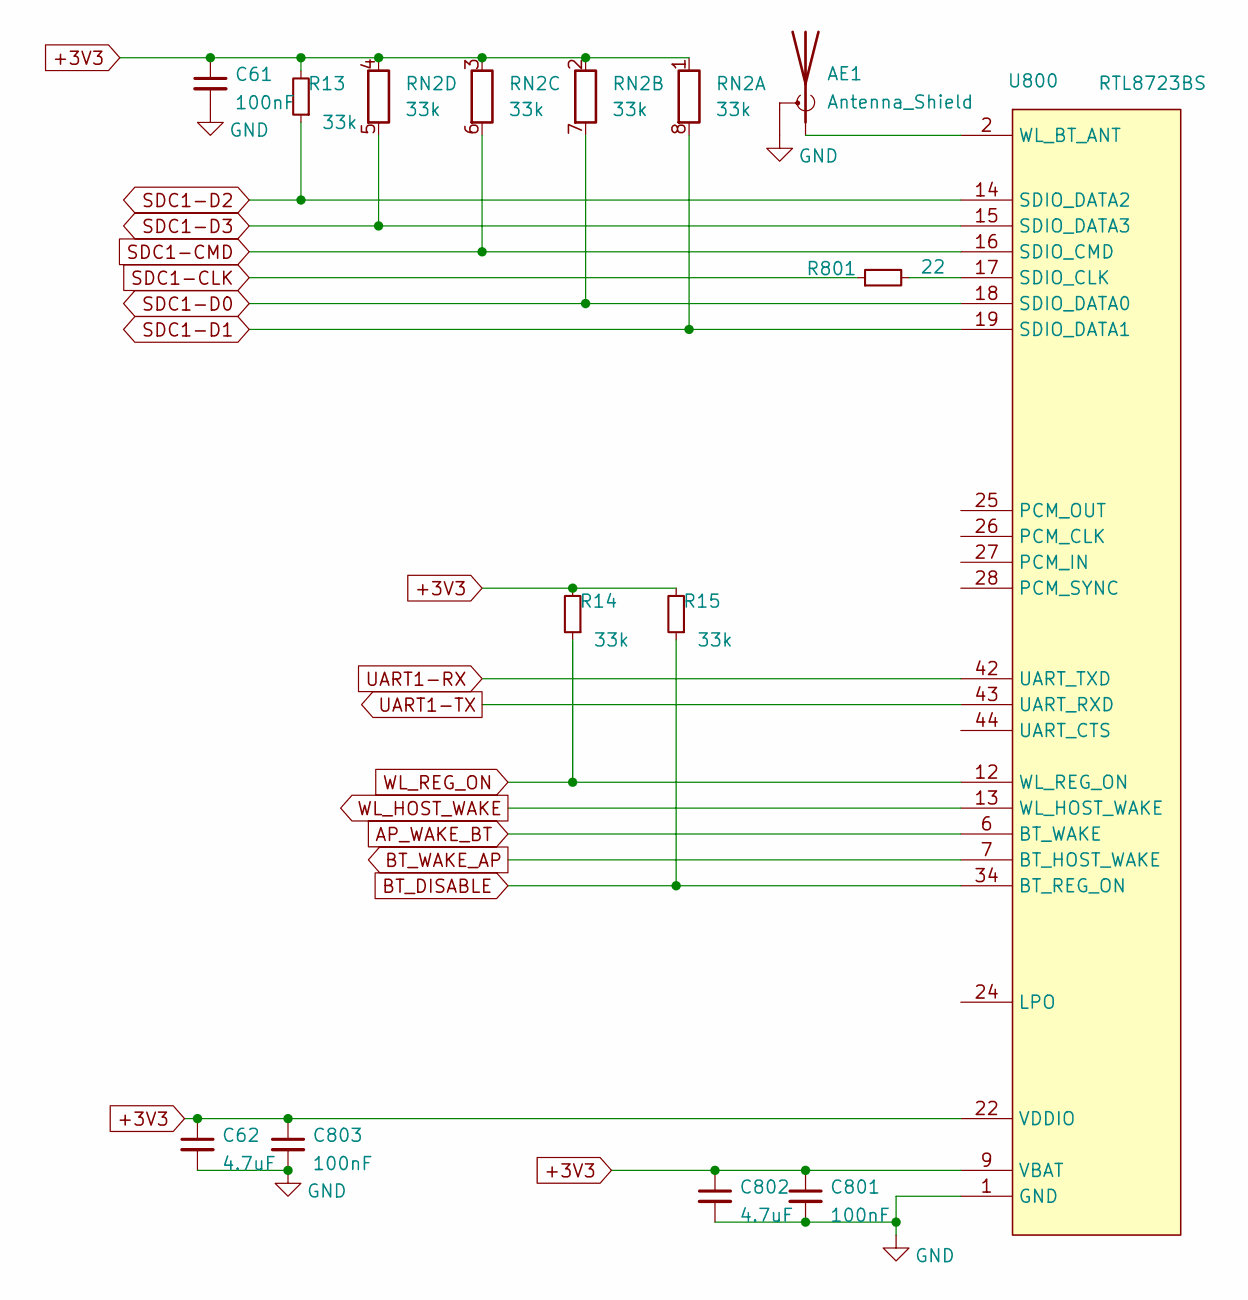
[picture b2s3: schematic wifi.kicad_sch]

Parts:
AE1: Antenna_Shield; U.FL_Hirose_U.FL-R-SMT-1_Vertical
C61, C801, C803: 100nF; C_0402_1005Metric
C62, C802: 4.7uF; C_0603_1608Metric
R13, R14, R15: 33k; R_0402_1005Metric
R801: 22; R_0402_1005Metric
RN2: 33k; R_Array_Concave_4x0402
U800: RTL8723BS; lga44_12x12mm_P0.9

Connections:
+3V3: C61.1, C62.1, C801.1, C802.1, C803.1, R13.2, R14.2, R15.2, RN2.1 (R1.1), RN2.2 (R2.1), RN2.3 (R3.1), RN2.4 (R4.1), U800.9 (VBAT), U800.22 (VDDIO); also elsewhere on the board
AP_WAKE_BT: U800.6 (BT_WAKE); also elsewhere on the board
BT_DISABLE: R15.1, U800.34 (BT_REG_ON); also elsewhere on the board
BT_WAKE_AP: U800.7 (BT_HOST_WAKE); also elsewhere on the board
GND: AE1.2 (Shield), C61.2, C62.2, C801.2, C802.2, C803.2, U800.1 (GND), U800.3 (GND), U800.20 (GND), U800.31 (GND), U800.33 (GND), U800.36 (GND), U800.41 (GND); also elsewhere on the board
unnamed: AE1.1 (A), U800.2 (WL_BT_ANT)
unnamed: R801.2, U800.17 (SDIO_CLK)
SDC1-CLK: R801.1; also elsewhere on the board
SDC1-CMD: RN2.6 (R3.2), U800.16 (SDIO_CMD); also elsewhere on the board
SDC1-D0: RN2.7 (R2.2), U800.18 (SDIO_DATA0); also elsewhere on the board
SDC1-D1: RN2.8 (R1.2), U800.19 (SDIO_DATA1); also elsewhere on the board
SDC1-D2: R13.1, U800.14 (SDIO_DATA2); also elsewhere on the board
SDC1-D3: RN2.5 (R4.2), U800.15 (SDIO_DATA3); also elsewhere on the board
UART1-RX: U800.42 (UART_TXD); also elsewhere on the board
UART1-TX: U800.43 (UART_RXD); also elsewhere on the board
WL_HOST_WAKE: U800.13 (WL_HOST_WAKE); also elsewhere on the board
WL_REG_ON: R14.1, U800.12 (WL_REG_ON); also elsewhere on the board

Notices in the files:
hardware/module.kicad_pcb:
© VDRD
module.kicad_pcb:
© VDRD 2024
